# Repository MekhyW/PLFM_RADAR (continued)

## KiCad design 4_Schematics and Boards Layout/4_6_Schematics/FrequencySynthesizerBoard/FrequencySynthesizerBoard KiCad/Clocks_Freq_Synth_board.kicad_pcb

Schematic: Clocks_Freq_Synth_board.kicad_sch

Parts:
C1, C62, C63, C85, C86, C89: 10pF; C0201
C2, C6: 0.33µF; C0201
C3: 0.47µf; C0201
C4, C5, C7: C-EUC0201; C0201
C8: 1000pF; C0201
C9, C10: 0.47µF; C0201
C11, C12, C13, C14, C59, C68, C69, C70, C71, C82: 1µF; C0201
C15, C17, C19: 10nF; C0402
C16, C18, C20, C22, C24, C26, C28, C30, C32, C34, C35, C36, C37, C41, C42, C43, C44, C64, C65, C66, C67, C87, C88, C90, C91: 0.1µF; C0201
C21, C25, C29, C33, C46, C51: 22µF; C1210
C23, C27, C31, C45, C47: 10µF; C1210
C38, C39, C40, C48, C49, C50, C55, C56, C57, C58, C72, C73, C74, C75, C76, C77, C78, C79, C80, C81: 4.7µF; C0201
C60, C83: 31pF; C0201
C61, C84: 10nF; C0201
C92: 0.1µf; C0201
D1, D2: Green; LED-0603
FB1, FB2, FB3, FB4: FBMH1608HL601-T; BEADC1608X90N
IC1: AD9523BCPZ; QFN50P1000X1000X100-73N
J1, J2, J5, J6, J7, J8, J9, J10, J11, J12, J13: 142-0731-211; 1420731211
J3, J4: CJT-T-P-HH-ST-TH1; CONN_CJT-T-P-XX-ST-TH1_SAI
JP1: PINHD-2X6; 2X06
JP2: PINHD-2X7; 2X07
L1, L2, L3, L4, L5, L6, L7, L8: 1.3nH; L0201
L9, L10, L11, L12, L13: L-EUL5650M; L5650M
R1, R12, R13, R26: 100R; R0201
R2, R3, R4, R7, R9, R11: 1k; R0201
R5, R14, R15, R19, R20, R27, R28, R32, R33: 0R; R0201
R6, R8, R10: 0.65k; R0201
R16, R29: 931R; R0201
R17, R30: 30R; R0201
R18, R31: 330R; R0201
R21, R34: 500R; R0201
R22, R23, R24, R25, R35, R36, R37, R38: 200k; R0201
R39, R40, R41: 22R; R0201
U1, U6: ADF4382ABCCZ; CC-48-10_ADI
U2, U3, U7, U9: MTX2-143+; DQ1225_MNC
U4, U5, U8, U10: ATS1005-3DB-FD-T05; SMT_DB-FD-T05_SUS
X4: ECOC-2522-100.000-3HC; SMD5_ECOC-2522_25P4X22_ECS
X5, X6: CVHD-950-50.000; SMD4_CVHD-950_CRX
X10, X11, X12, X13, X14, X15: 22-23-2021

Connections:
10MHZ_OUT: IC1.3 (REFA), X4.4 (OUTPUT)
100MHZ_OUT: IC1.5 (REFB), X5.3 (OUT)
+1V8_CLOCK: C31.1, C35.1, C36.1, C37.1, C41.1, C42.1, C43.1, C44.1, IC1.30 (VDD1.8_OUT[12:13]), IC1.36 (VDD1.8_OUT[10:11]), IC1.42 (VDD1.8_OUT[8:9]), IC1.48 (VDD1.8_OUT[6:7]), IC1.54 (VDD1.8_OUT[4:5]), IC1.63 (VDD1.8_OUT[0:3]), IC1.69 (VDD1.8_PLL2), L11.1
+3V3_CLOCK: C16.1, C18.1, C20.1, C22.1, C24.1, C26.1, C27.1, C28.1, C30.1, C32.1, C34.1, IC1.2 (VDD3_PLL1), IC1.13 (VDD3_PLL2), IC1.18 (VDD3_REF), IC1.27 (VDD3_OUT[12:13]), IC1.33 (VDD3_OUT[10:11]), IC1.39 (VDD3_OUT[8:9]), IC1.45 (VDD3_OUT[6:7]), IC1.51 (VDD3_OUT[4:5]), IC1.60 (VDD3_OUT[2:3]), IC1.66 (VDD3_OUT[0:1]), L10.1
+3V3_LO_1: C38.1, C39.1, C40.1, C45.1, C48.1, C49.1, C50.1, C72.1, C77.1, C78.1, C79.1, C80.1, C81.1, L12.1, R24.2, R25.2, R37.2, R38.2, U1.3 (V3_NDIV), U1.30 (V3_LS), U1.36 (V3_LDO), U1.40 (V3_SYNC), U1.44 (V3_REF), U1.45 (V3_PFD), U6.3 (V3_NDIV), U6.30 (V3_LS), U6.36 (V3_LDO), U6.40 (V3_SYNC), U6.44 (V3_REF), U6.45 (V3_PFD)
+3V3_XO: C23.1, L9.1, R2.2, X4.3 (SUPPLY_VOLTAGE), X5.4 (VDD), X6.4 (VDD)
+5V0_LO: C51.1, FB1.1, FB2.1, FB3.2, FB4.2, X15.1
AD9523_CS: JP1.5, R10.1
AD9523_EEPROM_SEL: IC1.57 (EEPROM_SEL), JP1.11
AD9523_OUT0_N: C11.2, IC1.67 (~OUT0)
AD9523_OUT0_P: C12.2, IC1.68 (OUT0)
AD9523_OUT1_N: C68.2, IC1.64 (~OUT1)
AD9523_OUT1_P: C69.2, IC1.65 (OUT1)
AD9523_OUT2+: IC1.62 (OUT2)
AD9523_OUT2-: IC1.61 (~OUT2)
AD9523_OUT3+: IC1.59 (OUT3)
AD9523_OUT3-: IC1.58 (~OUT3)
AD9523_OUT4_N: IC1.52 (~OUT4), J3.2
AD9523_OUT4_P: IC1.53 (OUT4), J3.1
AD9523_OUT5_N: IC1.49 (~OUT5), J4.2
AD9523_OUT5_P: IC1.50 (OUT5), J4.1
AD9523_OUT6+: C15.2, J7.1
AD9523_OUT7+: IC1.44 (OUT7), J8.1
AD9523_OUT8_N: C70.2, IC1.40 (~OUT8)
AD9523_OUT8_P: C71.2, IC1.41 (OUT8)
AD9523_OUT9_N: C13.2, IC1.37 (~OUT9)
AD9523_OUT9_P: C14.2, IC1.38 (OUT9)
AD9523_OUT10+: IC1.35 (OUT10), R40.1
AD9523_OUT11+: IC1.32 (OUT11), R41.1
AD9523_PD: IC1.15 (~PD), JP1.1
AD9523_REF_SEL: IC1.16 (REF_SEL), JP1.2
AD9523_RESET: IC1.19 (~RESET), JP1.4
AD9523_SCLK: JP1.6, R6.1
AD9523_SDIO: JP1.7, R8.1
AD9523_SDO: IC1.23 (SDO), JP1.8
AD9523_STATUS0: IC1.56 (STATUS0/SP0), JP1.9
AD9523_STATUS1: IC1.55 (STATUS1/SPI), JP1.10
AD9523_SYNC: IC1.17 (~SYNC), JP1.3
ADF4382_RX_CE: JP2.10, R38.1, U6.31 (CE)
ADF4382_RX_CS: JP2.9, R37.1, U6.32 (CSB)
ADF4382_RX_DELADJ: JP2.12, R35.2, U6.28 (DELADJ)
ADF4382_RX_DELSTR: JP2.11, R36.2, U6.29 (DELSTR)
ADF4382_RX_LKDET: JP2.13, R34.2, U6.27 (LKDET)
ADF4382_RX_SYNC_N: C70.1, R26.2, U6.39 (SYNCN)
ADF4382_RX_SYNC_P: C71.1, R26.1, U6.38 (SYNCP)
ADF4382_SCLK: JP2.2, U1.34 (SCLK), U6.34 (SCLK)
ADF4382_SDIO: JP2.3, U1.33 (SDIO), U6.33 (SDIO)
ADF4382_SDO: JP2.1, U1.35 (SDO), U6.35 (SDO)
ADF4382_TX_CE: JP2.5, R25.1, U1.31 (CE)
ADF4382_TX_CS: JP2.4, R24.1, U1.32 (CSB)
ADF4382_TX_DELADJ: JP2.7, R22.2, U1.28 (DELADJ)
ADF4382_TX_DELSTR: JP2.6, R23.2, U1.29 (DELSTR)
ADF4382_TX_LKDET: JP2.8, R21.2, U1.27 (LKDET)
ADF4382_TX_SYNC_N: C13.1, R13.2, U1.39 (SYNCN)
ADF4382_TX_SYNC_P: C14.1, R13.1, U1.38 (SYNCP)
GND: C1.2, C2.2, C3.1, C4.1, C5.1, C6.1, C7.1, C9.1, C10.1, C16.2, C18.2, C20.2, C21.2, C22.2, C23.2, C24.2, C25.2, C26.2, C27.2, C28.2, C29.2, C30.2, C31.2, C32.2, C33.2, C34.2, C35.2, C36.2, C37.2, C38.2, C39.2, C40.2, C41.2, C42.2, C43.2, C44.2, C45.2, C46.2, C47.2, C48.2, C49.2, C50.2, C51.2, C55.2, C56.2, C57.2, C58.2, C59.1, C60.2, C61.2, C62.2, C63.2, C72.2, C73.2, C74.2, C75.2, C76.2, C77.2, C78.2, C79.2, C80.2, C81.2, C82.1, C83.2, C84.2, C85.2, C86.2, C89.2, D1.C, D2.C, IC1.73 (EP), J1.2, J1.3, J1.4, J1.5, J2.2, J2.3, J2.4, J2.5, J5.2, J5.3, J5.4, J5.5, J6.2, J6.3, J6.4, J6.5, J7.2, J7.3, J7.4, J7.5, J8.2, J8.3, J8.4, J8.5, J9.2, J9.3, J9.4, J9.5, J10.2, J10.3, J10.4, J10.5, J11.2, J11.3, J11.4, J11.5, J12.2, J12.3, J12.4, J12.5, J13.2, J13.3, J13.4, J13.5, JP1.12, JP2.14, R3.1, R7.2, R9.2, R11.2, R22.1, R23.1, R35.1, R36.1, U1.1 (GND_2), U1.2 (GND_3), U1.4 (GND_4), U1.10 (GND_5), U1.12 (GND_6), U1.14 (GND_7), U1.16 (GND_8), U1.18 (GND_9), U1.19 (GND_10), U1.21 (GND_11), U1.23 (GND_12), U1.25 (GND_13), U1.26 (GND_14), U1.41 (GND_15), U1.48 (GND_16), U1.49 (GND_17), U1.50 (GND_18), U1.51 (GND_19), U1.52 (GND), U2.1 (EXTERNAL_GND_2), U2.3 (EXTERNAL_GND_3), U2.6 (EXTERNAL_GND_4), U2.10 (EXTERNAL_GND_5), U2.13 (EXTERNAL_GND), U3.1 (EXTERNAL_GND_2), U3.3 (EXTERNAL_GND_3), U3.6 (EXTERNAL_GND_4), U3.10 (EXTERNAL_GND_5), U3.13 (EXTERNAL_GND), U4.3 (GND_2), U4.4 (GND), U5.3 (GND_2), U5.4 (GND), U6.1 (GND_2), U6.2 (GND_3), U6.4 (GND_4), U6.10 (GND_5), U6.12 (GND_6), U6.14 (GND_7), U6.16 (GND_8), U6.18 (GND_9), U6.19 (GND_10), U6.21 (GND_11), U6.23 (GND_12), U6.25 (GND_13), U6.26 (GND_14), U6.41 (GND_15), U6.48 (GND_16), U6.49 (GND_17), U6.50 (GND_18), U6.51 (GND_19), U6.52 (GND), U7.1 (EXTERNAL_GND_2), U7.3 (EXTERNAL_GND_3), U7.6 (EXTERNAL_GND_4), U7.10 (EXTERNAL_GND_5), U7.13 (EXTERNAL_GND), U8.3 (GND_2), U8.4 (GND), U9.1 (EXTERNAL_GND_2), U9.3 (EXTERNAL_GND_3), U9.6 (EXTERNAL_GND_4), U9.10 (EXTERNAL_GND_5), U9.13 (EXTERNAL_GND), U10.3 (GND_2), U10.4 (GND), X4.5 (GROUND), X5.2 (GND), X6.2 (GND), X10.2, X11.2, X12.2, X13.2, X14.2, X15.2
unnamed: R2.1, R3.2, X4.1 (VOLTAGE_CONTROL)
unnamed: C2.1, R4.1, X6.1 (VOLT_CONTROL)
unnamed: C3.2, IC1.1 (LDO_PLL1)
unnamed: C6.2, IC1.7 (LF1_EXT_CAP)
unnamed: C4.2, IC1.4 (~REFA)
unnamed: C5.2, IC1.6 (~REFB)
unnamed: C7.2, IC1.10 (~OSC_IN)
unnamed: C8.2, IC1.11 (LF2_EXT_CAP)
unnamed: C8.1, R5.1
unnamed: C9.2, IC1.14 (LDO_VCO), R5.2
unnamed: C10.2, IC1.12 (LDO_PLL2)
unnamed: IC1.21 (SCLK/SCL), R6.2, R7.1
unnamed: IC1.22 (SDIO/SDA), R8.2, R9.1
unnamed: IC1.20 (~CS), R10.2, R11.1
unnamed: C11.1, R12.2, U1.43 (REFN)
unnamed: C12.1, R12.1, U1.42 (REFP)
unnamed: C61.1, R18.2
unnamed: R14.1, U1.9 (V5_VCO)
unnamed: FB2.2, R14.2, U1.8 (V5_CAL)
unnamed: C59.2, FB3.1, U1.46 (V5_CP)
unnamed: R19.1, R20.2
unnamed: R15.1, U1.7 (VTUNE)
unnamed: R15.2, R16.2
unnamed: C60.1, R16.1, R17.2
unnamed: R17.1, R18.1, R19.2
unnamed: C62.1, R20.1, U1.47 (CP)
unnamed: U2.2 (PRIMARY_DOT), U4.1 (INPUT)
unnamed: C65.2, U2.7 (SECONDARY_DOT)
unnamed: J10.1, U4.2 (OUTPUT)
unnamed: C64.2, U2.9 (SECONDARY)
unnamed: C67.2, U3.7 (SECONDARY_DOT)
unnamed: C66.2, U3.9 (SECONDARY)
unnamed: U3.2 (PRIMARY_DOT), U5.1 (INPUT)
unnamed: J1.1, U5.2 (OUTPUT)
unnamed: D1.A, R21.1
unnamed: J9.1, U1.37 (MUXOUT)
unnamed: C68.1, R1.2, U6.43 (REFN)
unnamed: C69.1, R1.1, U6.42 (REFP)
unnamed: R27.1, U6.9 (V5_VCO)
unnamed: FB1.2, R27.2, U6.8 (V5_CAL)
unnamed: C82.2, FB4.1, U6.46 (V5_CP)
unnamed: C84.1, R31.2
unnamed: R32.1, R33.2
unnamed: R28.1, U6.7 (VTUNE)
unnamed: R28.2, R29.2
unnamed: C83.1, R29.1, R30.2
unnamed: R30.1, R31.1, R32.2
unnamed: C85.1, R33.1, U6.47 (CP)
unnamed: D2.A, R34.1
unnamed: J2.1, U6.37 (MUXOUT)
unnamed: C88.2, U7.7 (SECONDARY_DOT)
unnamed: C87.2, U7.9 (SECONDARY)
unnamed: U7.2 (PRIMARY_DOT), U8.1 (INPUT)
unnamed: J11.1, U8.2 (OUTPUT)
unnamed: C91.2, U9.7 (SECONDARY_DOT)
unnamed: C90.2, U9.9 (SECONDARY)
unnamed: U9.2 (PRIMARY_DOT), U10.1 (INPUT)
unnamed: J12.1, U10.2 (OUTPUT)
unnamed: C92.1, IC1.72 (~PLL_OUT)
unnamed: C92.2, J13.1
unnamed: IC1.47 (OUT6), R39.1
unnamed: C15.1, R39.2
unnamed: C17.2, J5.1
unnamed: C17.1, R40.2
unnamed: C19.2, J6.1
unnamed: C19.1, R41.2
unnamed: C21.1, L9.2, X10.1
unnamed: C25.1, L10.2, X11.1
unnamed: C29.1, L11.2, X12.1
unnamed: C33.1, L12.2, X13.1
unnamed: C46.1, L13.2, X14.1
OSC_CTRL: IC1.8 (OSC_CTRL), R4.2
RX_RFOUT_1_N: C87.1, L5.2, U6.20 (RFOUT1N)
RX_RFOUT_1_P: C88.1, L6.1, U6.22 (RFOUT1P)
RX_RFOUT_2_N: C90.1, L7.2, U6.15 (RFOUT2N)
RX_RFOUT_2_P: C91.1, L8.1, U6.17 (RFOUT2P)
TX_RFOUT_1_N: C64.1, L2.2, U1.20 (RFOUT1N)
TX_RFOUT_1_P: C65.1, L3.1, U1.22 (RFOUT1P)
TX_RFOUT_2_N: C66.1, L1.2, U1.15 (RFOUT2N)
TX_RFOUT_2_P: C67.1, L4.1, U1.17 (RFOUT2P)
VCXO_OUT: IC1.9 (OSC_IN), X6.3 (OUT)

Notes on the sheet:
L9 to L13: MPN HI2220P601R-10 FERRITE BEAD 600 OHM 2220 (5650) 1LN
C:/Users/ASUS/Desktop/RADAR_V5/EagleFiles/FrequencySynthesizerBoard/clock_planning.bmp
60 MHz
Jitter Cleaner, Clock Generator & Frequency Synthesizer
CCHD-950-100.000
CVHD-950-100.000

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
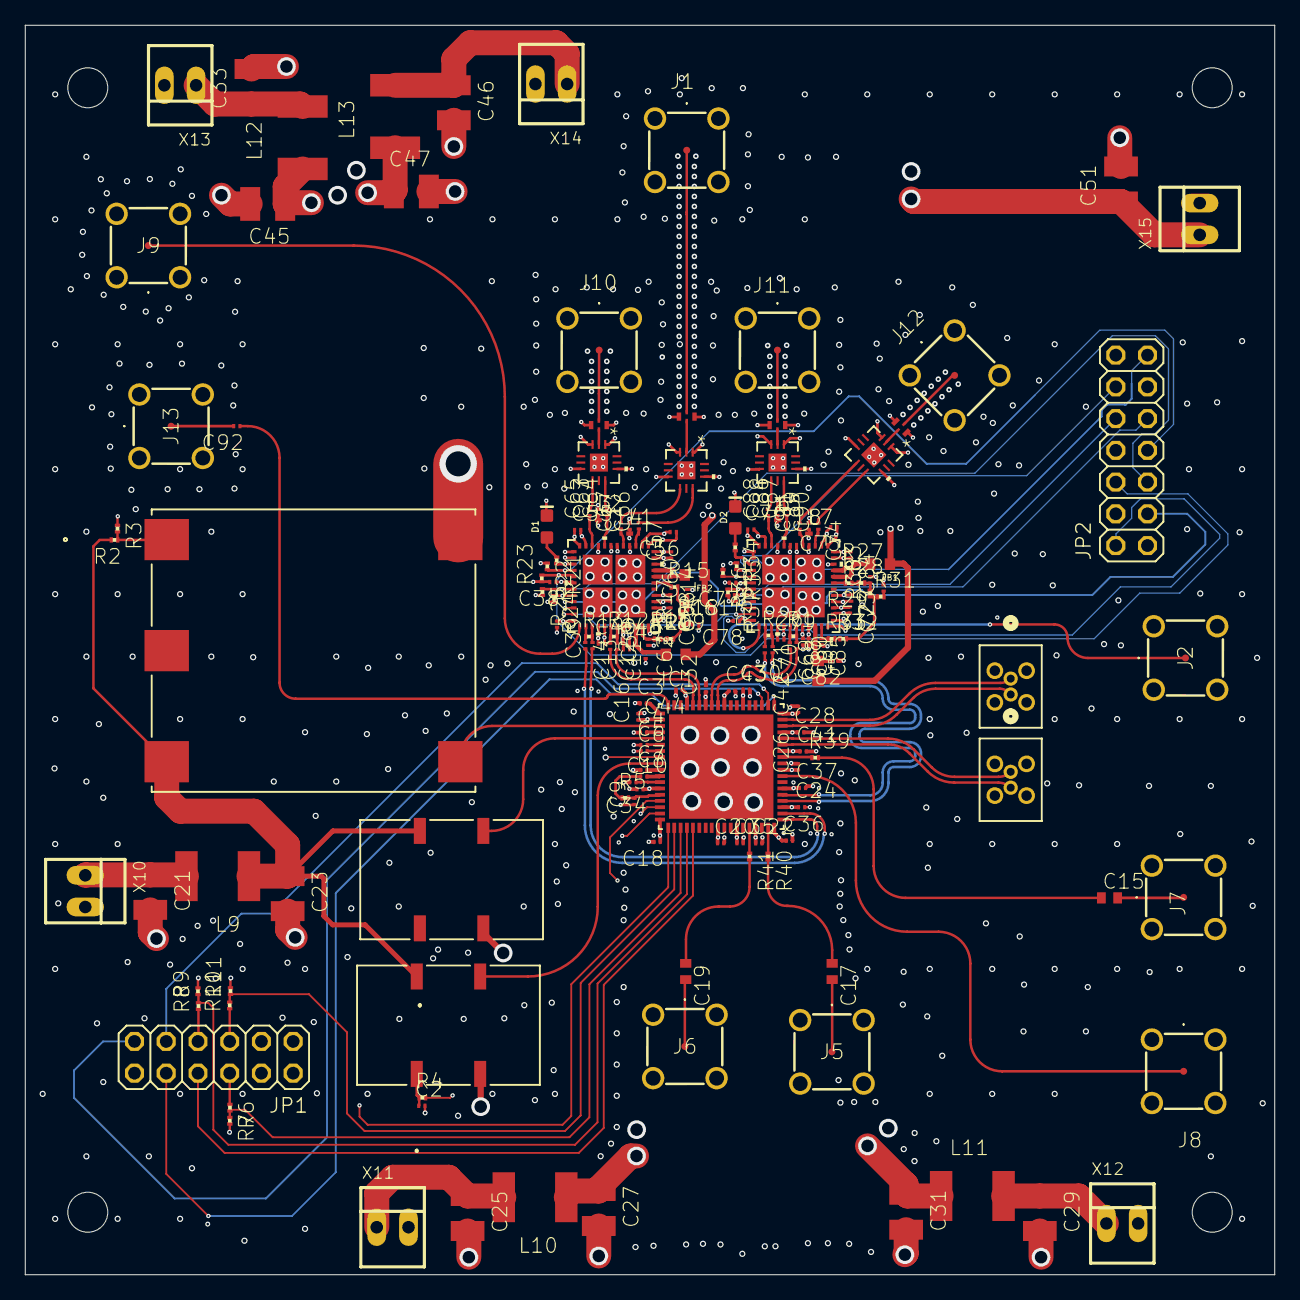
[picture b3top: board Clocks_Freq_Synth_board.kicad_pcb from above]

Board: 6 copper layers, 100.0 x 100.0 mm, 188 parts (0 on the bottom side), 134 nets.

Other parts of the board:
UNK_HOLE_0: dummyfp0
UNK_HOLE_1: dummyfp1
UNK_HOLE_2: dummyfp2
UNK_HOLE_3: dummyfp3

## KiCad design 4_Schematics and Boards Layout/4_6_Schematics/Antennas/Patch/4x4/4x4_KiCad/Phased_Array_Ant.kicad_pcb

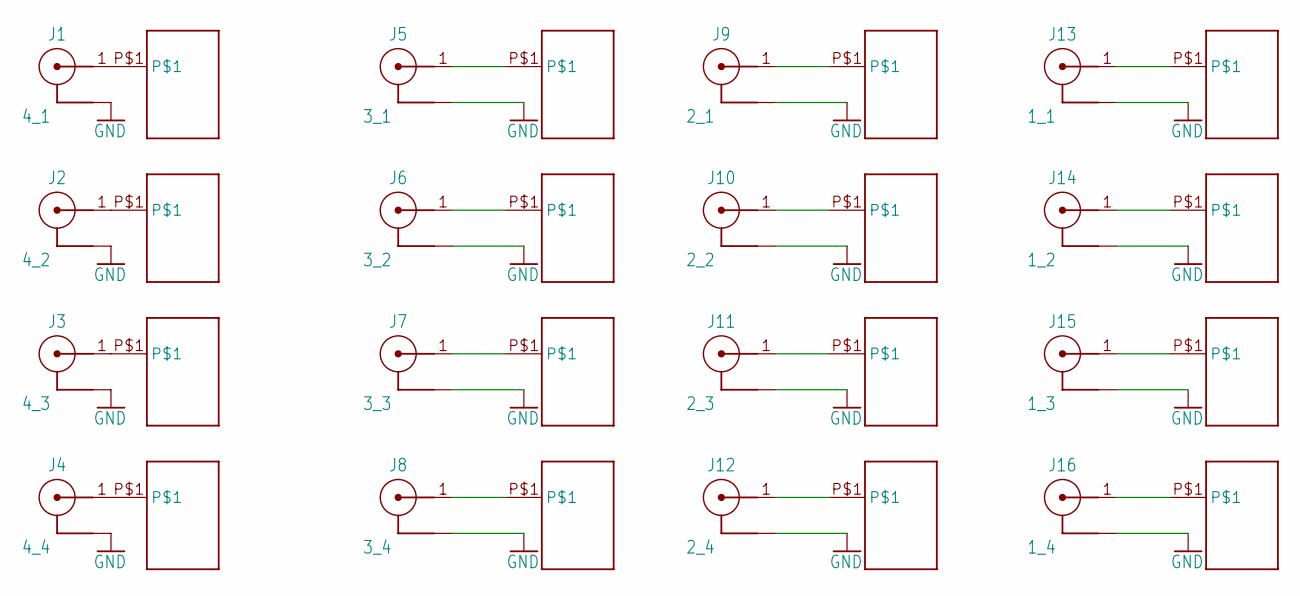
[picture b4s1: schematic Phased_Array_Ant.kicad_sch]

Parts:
J1: 4_1; 60124102122403
J2: 4_2; 60124102122403
J3: 4_3; 60124102122403
J4: 4_4; 60124102122403
J5: 3_1; 60124102122403
J6: 3_2; 60124102122403
J7: 3_3; 60124102122403
J8: 3_4; 60124102122403
J9: 2_1; 60124102122403
J10: 2_2; 60124102122403
J11: 2_3; 60124102122403
J12: 2_4; 60124102122403
J13: 1_1; 60124102122403
J14: 1_2; 60124102122403
J15: 1_3; 60124102122403
J16: 1_4; 60124102122403
U$1, U$2, U$3, U$4, U$5, U$6, U$7, U$8, U$9, U$10, U$11, U$12, U$13, U$14, U$15, U$16: 10.5GHZ_ANT

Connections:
GND: J1.2, J1.3 (2), J1.4 (2), J2.2, J2.3 (2), J2.4 (2), J3.2, J3.3 (2), J3.4 (2), J4.2, J4.3 (2), J4.4 (2), J5.2, J5.3 (2), J5.4 (2), J6.2, J6.3 (2), J6.4 (2), J7.2, J7.3 (2), J7.4 (2), J8.2, J8.3 (2), J8.4 (2), J9.2, J9.3 (2), J9.4 (2), J10.2, J10.3 (2), J10.4 (2), J11.2, J11.3 (2), J11.4 (2), J12.2, J12.3 (2), J12.4 (2), J13.2, J13.3 (2), J13.4 (2), J14.2, J14.3 (2), J14.4 (2), J15.2, J15.3 (2), J15.4 (2), J16.2, J16.3 (2), J16.4 (2)
unnamed: J1.1, U$1.P$1
unnamed: J2.1, U$2.P$1
unnamed: J3.1, U$3.P$1
unnamed: J4.1, U$4.P$1
unnamed: J5.1, U$5.P$1
unnamed: J6.1, U$6.P$1
unnamed: J7.1, U$7.P$1
unnamed: J8.1, U$8.P$1
unnamed: J9.1, U$9.P$1
unnamed: J10.1, U$10.P$1
unnamed: J11.1, U$11.P$1
unnamed: J12.1, U$12.P$1
unnamed: J13.1, U$13.P$1
unnamed: J14.1, U$14.P$1
unnamed: J15.1, U$15.P$1
unnamed: J16.1, U$16.P$1

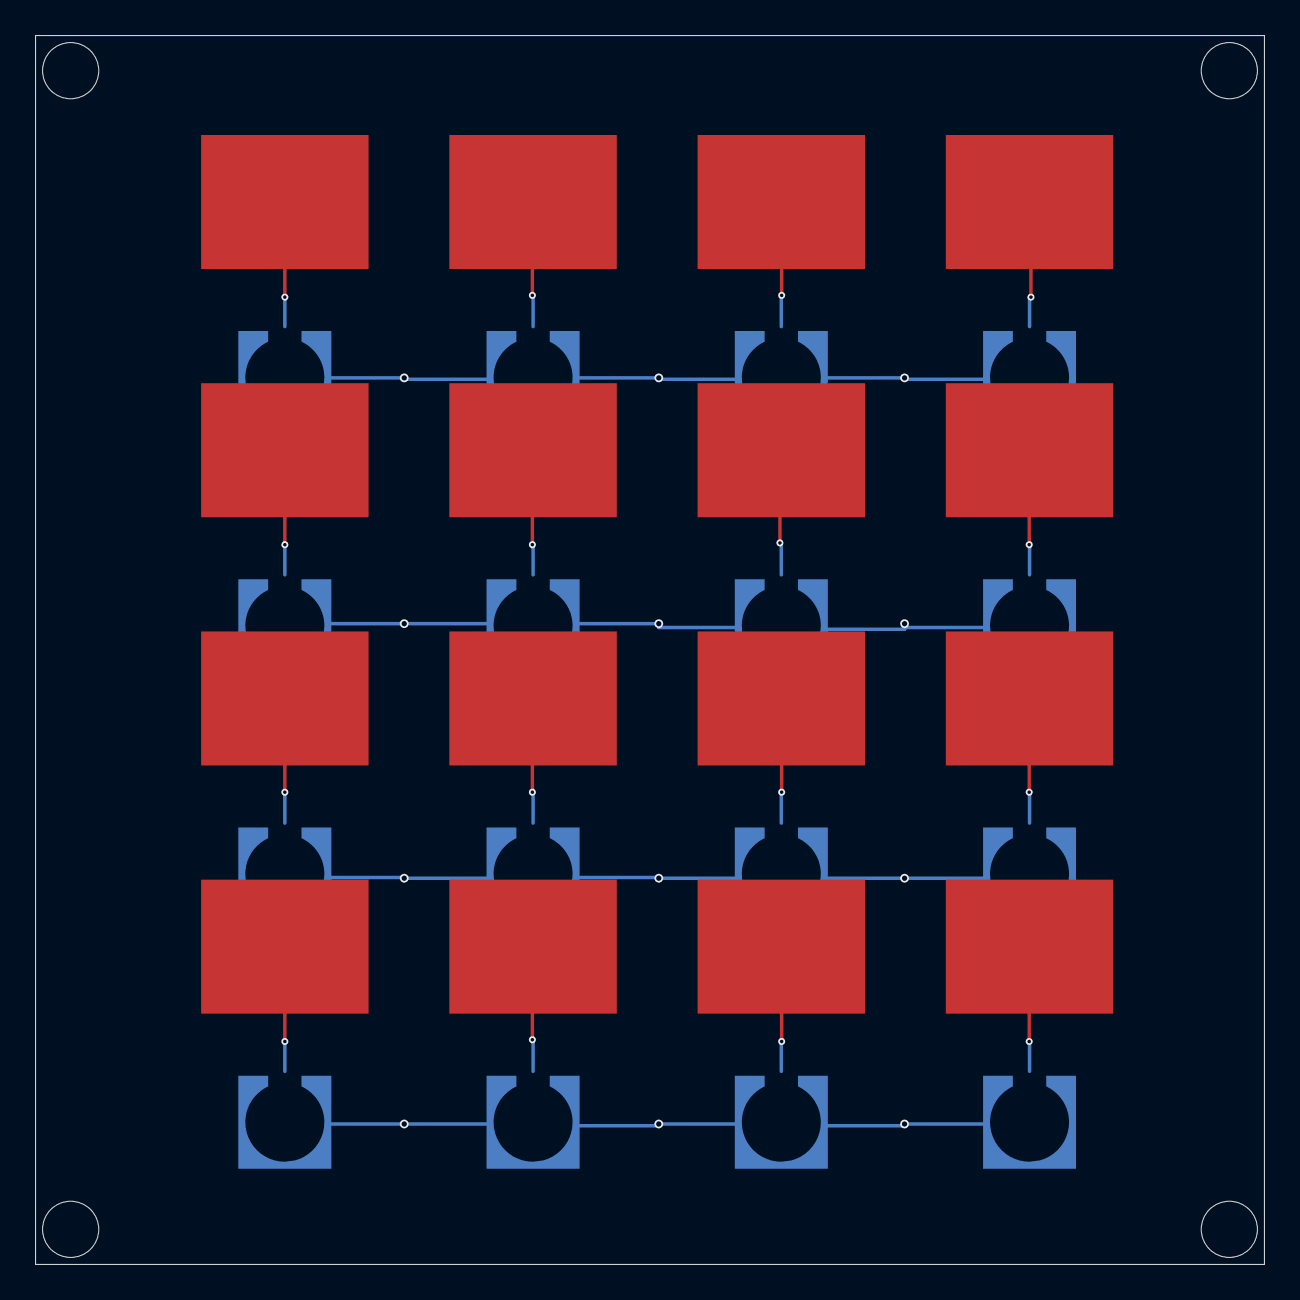
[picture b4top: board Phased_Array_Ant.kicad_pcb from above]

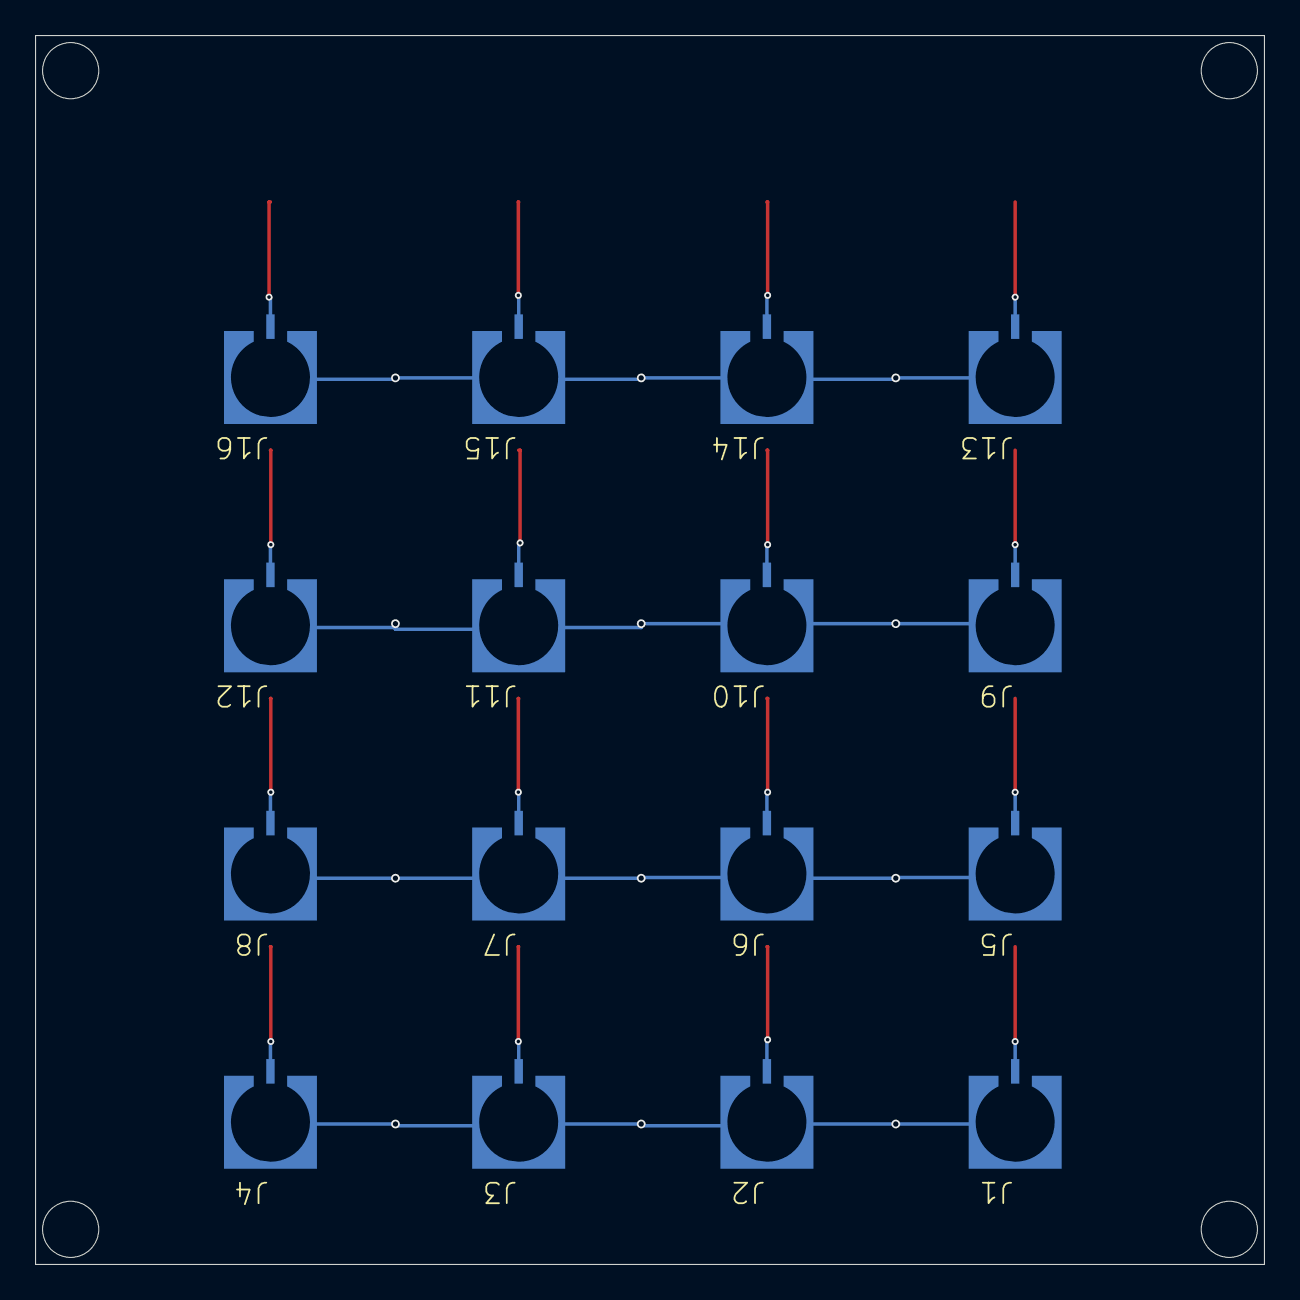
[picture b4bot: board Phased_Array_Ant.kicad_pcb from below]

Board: 6 copper layers, 70.0 x 70.0 mm, 36 parts (16 on the bottom side), 17 nets.

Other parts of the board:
UNK_HOLE_0: dummyfp0
UNK_HOLE_1: dummyfp1
UNK_HOLE_2: dummyfp2
UNK_HOLE_3: dummyfp3

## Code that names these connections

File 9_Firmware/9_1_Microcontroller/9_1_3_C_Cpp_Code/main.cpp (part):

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};

// Convenience HAL wrappers for AD9523 control pins (GPIOF as you said)
static inline void AD9523_PD(bool v)        { HAL_GPIO_WritePin(GPIOF, AD9523_PD_Pin, v ? GPIO_PIN_SET : GPIO_PIN_RESET); }
static inline void AD9523_REF_SEL(bool v)   { HAL_GPIO_WritePin(GPIOF, AD9523_REF_SEL_Pin, v ? GPIO_PIN_SET : GPIO_PIN_RESET); }
static inline void AD9523_SYNC_PULSE(void)  { HAL_GPIO_WritePin(GPIOF, AD9523_SYNC_Pin, GPIO_PIN_SET); HAL_Delay(1); HAL_GPIO_WritePin(GPIOF, AD9523_SYNC_Pin, GPIO_PIN_RESET); }
static inline void AD9523_RESET_ASSERT()    { HAL_GPIO_WritePin(GPIOF, AD9523_RESET_Pin, GPIO_PIN_RESET); } // check polarity
static inline void AD9523_RESET_RELEASE()   { HAL_GPIO_WritePin(GPIOF, AD9523_RESET_Pin, GPIO_PIN_SET); }
static inline void AD9523_CS(bool v)        { HAL_GPIO_WritePin(GPIOF, AD9523_CS_Pin, v ? GPIO_PIN_SET : GPIO_PIN_RESET); }
static inline void AD9523_EEPROM_SEL(bool v){ HAL_GPIO_WritePin(GPIOF, AD9523_EEPROM_SEL_Pin, v ? GPIO_PIN_SET : GPIO_PIN_RESET); }

/* USER CODE END PV */

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    static uint32_t last_clock_check = 0;
    if (HAL_GetTick() - last_clock_check > 5000) {
        last_clock_check = HAL_GetTick();   // commit the rate-limit window first
        GPIO_PinState s0 = HAL_GPIO_ReadPin(AD9523_STATUS0_GPIO_Port, AD9523_STATUS0_Pin);
        GPIO_PinState s1 = HAL_GPIO_ReadPin(AD9523_STATUS1_GPIO_Port, AD9523_STATUS1_Pin);
        DIAG_GPIO("CLK", "AD9523 STATUS0", s0);
        DIAG_GPIO("CLK", "AD9523 STATUS1", s1);
        if (s0 == GPIO_PIN_RESET || s1 == GPIO_PIN_RESET) {
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
  DIAG_SECTION("AD9523 POWER SEQUENCING");
  DIAG("PWR", "Asserting AD9523 reset (pin LOW)");
  HAL_GPIO_WritePin(AD9523_RESET_GPIO_Port,AD9523_RESET_Pin,GPIO_PIN_RESET);

  //Power sequencing AD9523
  DIAG("PWR", "Enabling 1.8V clock rail");
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
  // check if there is a lock via direct GPIO (independent of register read above)
  DIAG("LO", "Direct GPIO lock detect pins:");
  DIAG_GPIO("LO", "ADF4382_TX_LKDET", ADF4382_TX_LKDET_GPIO_Port, ADF4382_TX_LKDET_Pin);
  DIAG_GPIO("LO", "ADF4382_RX_LKDET", ADF4382_RX_LKDET_GPIO_Port, ADF4382_RX_LKDET_Pin);
  if(HAL_GPIO_ReadPin (ADF4382_TX_LKDET_GPIO_Port, ADF4382_TX_LKDET_Pin))
  {
      // Set The LED_1 ON!
      HAL_GPIO_WritePin(LED_1_GPIO_Port, LED_1_Pin, GPIO_PIN_SET);
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      DIAG_WARN("LO", "TX NOT locked via GPIO -- LED_1 OFF");
  }

  if(HAL_GPIO_ReadPin (ADF4382_RX_LKDET_GPIO_Port, ADF4382_RX_LKDET_Pin))
  {
      // Set The LED_2 ON!
      HAL_GPIO_WritePin(LED_2_GPIO_Port, LED_2_Pin, GPIO_PIN_SET);
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  __HAL_RCC_GPIOD_CLK_ENABLE();

  /*Configure GPIO pin Output Level */
  HAL_GPIO_WritePin(GPIOF, AD9523_PD_Pin|AD9523_REF_SEL_Pin|AD9523_SYNC_Pin|AD9523_RESET_Pin
                          |AD9523_CS_Pin|AD9523_EEPROM_SEL_Pin|LED_1_Pin|LED_2_Pin
                          |LED_3_Pin|LED_4_Pin, GPIO_PIN_RESET);

  /*Configure GPIO pin Output Level */
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
  /*Configure GPIO pin Output Level */
  HAL_GPIO_WritePin(GPIOG, EN_P_5V0_PA1_Pin|EN_P_5V0_PA2_Pin|EN_P_5V0_PA3_Pin|EN_P_5V5_PA_Pin
                          |EN_P_1V8_CLOCK_Pin|EN_P_3V3_CLOCK_Pin|ADF4382_RX_DELADJ_Pin|ADF4382_RX_DELSTR_Pin
                          |ADF4382_RX_CE_Pin|ADF4382_RX_CS_Pin|ADF4382_TX_DELSTR_Pin|ADF4382_TX_DELADJ_Pin
                          |ADF4382_TX_CS_Pin|ADF4382_TX_CE_Pin, GPIO_PIN_RESET);

  /*Configure GPIO pin Output Level */
  HAL_GPIO_WritePin(GPIOE, EN_P_1V0_FPGA_Pin|EN_P_1V8_FPGA_Pin|EN_P_3V3_FPGA_Pin|EN_P_5V0_ADAR_Pin
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  /*Configure GPIO pin Output Level */
  HAL_GPIO_WritePin(GPIOB, DAC_1_VG_CLR_Pin|DAC_1_VG_LDAC_Pin|DAC_2_VG_CLR_Pin|DAC_2_VG_LDAC_Pin, GPIO_PIN_RESET);

  /*Configure GPIO pins : AD9523_PD_Pin AD9523_REF_SEL_Pin AD9523_SYNC_Pin AD9523_RESET_Pin
                           AD9523_CS_Pin AD9523_EEPROM_SEL_Pin LED_1_Pin LED_2_Pin
                           LED_3_Pin LED_4_Pin */
  GPIO_InitStruct.Pin = AD9523_PD_Pin|AD9523_REF_SEL_Pin|AD9523_SYNC_Pin|AD9523_RESET_Pin
                          |AD9523_CS_Pin|AD9523_EEPROM_SEL_Pin|LED_1_Pin|LED_2_Pin
                          |LED_3_Pin|LED_4_Pin;
  GPIO_InitStruct.Mode = GPIO_MODE_OUTPUT_PP;
  GPIO_InitStruct.Pull = GPIO_NOPULL;
  GPIO_InitStruct.Speed = GPIO_SPEED_FREQ_LOW;
  HAL_GPIO_Init(GPIOF, &GPIO_InitStruct);

  /*Configure GPIO pins : AD9523_STATUS0_Pin AD9523_STATUS1_Pin */
  GPIO_InitStruct.Pin = AD9523_STATUS0_Pin|AD9523_STATUS1_Pin;
  GPIO_InitStruct.Mode = GPIO_MODE_INPUT;
  GPIO_InitStruct.Pull = GPIO_NOPULL;
  HAL_GPIO_Init(GPIOF, &GPIO_InitStruct);
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  HAL_GPIO_Init(GPIOA, &GPIO_InitStruct);

  /*Configure GPIO pins : EN_P_5V0_PA1_Pin EN_P_5V0_PA2_Pin EN_P_5V0_PA3_Pin EN_P_5V5_PA_Pin
                           EN_P_1V8_CLOCK_Pin EN_P_3V3_CLOCK_Pin ADF4382_RX_DELADJ_Pin ADF4382_RX_DELSTR_Pin
                           ADF4382_RX_CE_Pin ADF4382_RX_CS_Pin ADF4382_TX_DELSTR_Pin ADF4382_TX_DELADJ_Pin
                           ADF4382_TX_CS_Pin ADF4382_TX_CE_Pin */
  GPIO_InitStruct.Pin = EN_P_5V0_PA1_Pin|EN_P_5V0_PA2_Pin|EN_P_5V0_PA3_Pin|EN_P_5V5_PA_Pin
                          |EN_P_1V8_CLOCK_Pin|EN_P_3V3_CLOCK_Pin|ADF4382_RX_DELADJ_Pin|ADF4382_RX_DELSTR_Pin
                          |ADF4382_RX_CE_Pin|ADF4382_RX_CS_Pin|ADF4382_TX_DELSTR_Pin|ADF4382_TX_DELADJ_Pin
                          |ADF4382_TX_CS_Pin|ADF4382_TX_CE_Pin;
  GPIO_InitStruct.Mode = GPIO_MODE_OUTPUT_PP;
  GPIO_InitStruct.Pull = GPIO_NOPULL;
  GPIO_InitStruct.Speed = GPIO_SPEED_FREQ_LOW;
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  HAL_NVIC_SetPriority(FPGA_FRAME_PULSE_EXTI_IRQn, 5, 0);
  HAL_NVIC_EnableIRQ(FPGA_FRAME_PULSE_EXTI_IRQn);

  /*Configure GPIO pins : ADF4382_RX_LKDET_Pin ADF4382_TX_LKDET_Pin */
  GPIO_InitStruct.Pin = ADF4382_RX_LKDET_Pin|ADF4382_TX_LKDET_Pin;
  GPIO_InitStruct.Mode = GPIO_MODE_INPUT;
  GPIO_InitStruct.Pull = GPIO_NOPULL;
  HAL_GPIO_Init(GPIOG, &GPIO_InitStruct);
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
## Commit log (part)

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2026-04-18 fix(fpga): registered reset fan-out at 400 MHz; default USB to FT2232H
    Replace direct !reset_n async sense with a registered active-high reset_h
    (max_fanout=50) in nco_400m_enhanced, cic_decimator_4x_enhanced, and
    ddc_400m. The prior single-LUT1 / 700+ load net was the root cause of
    WNS=-0.626 ns in the 400 MHz clock domain on the xc7a50t build. Vivado
    replicates the constrained register into ≈14 regional copies, each driving
    ≤50 loads, closing timing at 2.5 ns.
2026-04-23 ci(fpga): wire RX-B latency tests; fix downstream compile after inline-FFT removal
    - run_regression.sh: add frequency_matched_filter.v to PROD_RTL and RECEIVER_RTL
    compile groups (was implicitly required after inline behavioural FFT in
    matched_filter_processing_chain.v was removed); empty EXTRA_RTL with set -u
    guards; bump Matched Filter Chain timeout to 600s.
    - run_regression.sh: add two PHASE 3 tests — tb_rxb_latency_measure (chain
    pipeline depth) and tb_rxb_fullchain_latency (multi-segment + chain).
2026-04-23 perf(fpga): symmetric pre-adder FIR — 32→16 DSPs/channel (-32 total)
    Re-group the 32-tap symmetric lowpass into 16 (D+A)*B operations using
    the DSP48E1 pre-adder, exploiting coeff[k] == coeff[31-k]. Production
    silicon (XC7A50T) drops from 112/120 DSPs (93.3%) to 80/120 (66.7%),
    freeing the budget needed for the matched-filter FFT swap (RX-NEW-3).
    Bit-exact contract preserved at non-saturating signal levels: DC=5000
    → 8847 and 45 MHz tone → ±16 LSB match the unfolded design and the
2026-04-27 cleanup(fpga): RX-A1 — drop dead chirp_counter port from MF chain
    matched_filter_processing_chain declared `input wire [5:0] chirp_counter`
    but never read it inside the module. matched_filter_multi_segment passed
    its own chirp_counter through to that dead port.
    Removed the port from the chain and the corresponding hookup at the
    multi_segment instantiation site. Five testbenches also referenced the
    port (tb_mf_cosim, tb_matched_filter_processing_chain, tb_rxb_latency
2026-04-28 fix(mcu): MCU-A6 — recovery handlers for AD9523_CLOCK and FPGA_COMM
    attemptErrorRecovery() previously fell through to the default log-only
    branch for both ERROR_AD9523_CLOCK and ERROR_FPGA_COMM. checkSystemHealth
    keeps re-firing the same error every pass with no recovery action ever
    attempted, so the system limps along until escalation kicks in.
    ERROR_AD9523_CLOCK: AD9523_RESET_ASSERT, 10 ms settle, then re-run
    configure_ad9523() (releases reset, selects REFB, reprograms, waits for
2026-04-29 mcu(bmp180): call cal-coefficient init at boot + watchdog cadence fix (AUDIT-CAL)
    The BMP180 driver had no public init method and never called
    readCalibrationCoefficients() from anywhere -- _calCoeff ran at the
    C++ in-class member-initializer defaults (all zeros) at runtime.
    Consequence chain:
    - computeB5(UT) short-circuited via 0/0 (Cortex-M7 SDIV with
    SCB->CCR.DIV_0_TRP=0 returns 0 silently -- system_stm32f7xx.c does
2026-04-29 mcu(health): commit rate-limit window before early returns (AUDIT-CAL follow-up)
    checkSystemHealth() had three watchdog blocks with the identical
    "last_X_check not updated on error path" bug — same root cause as
    AUDIT-CAL (BMP180 fix in commit 95aed35), distinct sites:
    AD9523 clock check (5 s) main.cpp:693-705
    ADAR1000 comm check (2 s) main.cpp:729-749
    IMU comm check (10 s) main.cpp:752-760
2026-04-30 docs(fpga): correct matched_filter_processing_chain header (LogiCORE swap, FSM)
    The header still described the legacy in-house Radix-2 DIT fft_engine and a
    FWD/REF/INV BITREV+BUTTERFLY state list that no longer matches reality.
    Since RX-NEW-3 (commit 5c8cc8c), the chain instantiates fft_engine_axi_bridge,
    which wraps xfft_2048 — LogiCORE FFT v9.1 (Pipelined Streaming) in synth/XSim
    when FFT_USE_XILINX_IP is defined, in-house fft_engine fallback in iverilog.
    Bit-reversal is now handled inside the IP (and the fallback), so the FSM has
2026-04-30 chirp-v2 PR-D: chirp_scheduler replaces radar_mode_controller; MF/MTI wave_sel-native
    Single 100 MHz scheduler emits wave_sel[1:0] and chirp_pulse natively. Modes
    00 (STM32 pass-through), 01 (auto-scan over SHORT/MEDIUM/LONG sub-frames),
    10 (single-chirp debug), 11 (track dwell with watchdog scan-fallback after
    RP_DEF_TRACK_WATCHDOG_FRAMES=5 idle frames). Sub-frame mask lets ops drop a
    waveform without recompiling.
    Drops the receiver_final wave_sel shim added in PR-C: wave_sel comes
2026-05-01 fix(regression): allow leading whitespace in [PASS]/[FAIL] anchors
    Three regex sites (run_test, run_mf_cosim, run_doppler_cosim) anchored
    at column 0 with `^\[PASS|^\[FAIL`, but most TBs emit ` [PASS]` /
    ` [FAIL]` from `task check;` formatting. Anchors silently matched
    zero markers, the fallback "did anything reach $finish" path
    reported PASS, and 48 real failures across tb_system_e2e (×2 modes),
    tb_fft_engine, and tb_fullchain_realdata went unnoticed across PR-D..G.
2026-05-01 test(fft): PR-L — fix tb_fft_engine N=32→16 dropdown bugs (T-4)
    The TB hard-coded /32.0 in cosine/sine angle math and read out_re[28] /
    out_re[30] which don't exist for N=16, so 3/12 checks failed (Test 3
    single-tone, Test 7 imag-tone). Pure TB math error — fft_engine.v is
    correct (proven by every production MF/Doppler cosim passing bit-exact).
    Test 3: /32.0 → /N, peak expected = N/2*1000 = 8000 (not 16000),
    conjugate read at bin N-4=12 (not 28).
2026-05-01 fix(fpga): C-4 — replace IDDR DDR demux with negedge IFF for AD9484 SDR
    The AD9484 is SDR LVDS — datasheet p.5 lists "Output (LVDS—SDR)" as the
    only output mode and p.16 confirms "data outputs are valid on the rising
    edge of DCO." DCO runs at fs (400 MHz), one new sample per period, held
    stable across the period. There is no DDR mode and no SPI access (CSB is
    tied to +1V8 on the production board, RADAR_Main_Board.sch:46719).
    ad9484_interface_400m.v previously instantiated an IDDR per data bit and
2026-05-02 fix(fpga): PR-O.8.1 — drop stale BFP-era ports, fix xsim include path
    Wrapper xfft_2048.v had m_axis_data_tuser and m_axis_status_{tdata,tvalid,
    tready} hooked up to the IP, but the regenerated xfft_2048_ip in scaled
    mode + Pipelined Streaming + 1 channel + no XK_INDEX/OVFLO doesn't expose
    those ports. xelab errored "cannot find port" on all four. Removed.
    run_xfft_xsim.sh missed -i "$PROJ_ROOT" so xvlog couldn't resolve
    `include "radar_params.vh"` from inside tb/. Fixed.
2026-05-02 test(fpga): PR-Q.2 — align cosim T_PRI_MEDIUM 175->161 us + regen goldens
    Mirror the PR-Q.1 PRI stagger (MEDIUM 175 us -> 161 us) into the cosim
    scenario generator and regenerate all 12 affected golden hex/csv files.
    Without this, the Doppler co-sim TBs would diverge from the RTL on every
    MEDIUM sub-frame bin.
    - tb/cosim/radar_scene.py: T_PRI_MEDIUM = 161e-6
    - tb/cosim/gen_doppler_golden.py: comment update for MEDIUM bin map
2026-05-02 fix(gui): P-4 — dashboard NUM_RANGE_BINS 64 → 512 (import from radar_protocol)
    dashboard.py:77 had a stale `NUM_RANGE_BINS = 64` literal from pre-PR-F.
    Range-Doppler canvas was mis-sized: parser at radar_protocol.py:425
    already enforces 512, so production frames would never have rendered
    correctly even with P-2/P-3 in place.
    Fix: drop the local literals; re-export NUM_RANGE_BINS / NUM_DOPPLER_BINS
    through v7/hardware.py (which already re-exports the rest of
2026-05-02 fix(gui): P-6 / PR-Q.6 — workers route detections through CRT extractor (C-5)
    Both live and replay paths used the legacy single-PRI extractor with the
    LONG-PRI v_res placeholder, which yielded wrong velocities for the SHORT
    and MEDIUM sub-frames. PR-Q.5 already provided extract_targets_from_frame_crt
    (48-bin, 3-PRI Chinese-Remainder-Theorem unfolding) — this PR wires it in.
    Changes:
    - workers.py imports extract_targets_from_frame_crt at module scope.
2026-05-02 sim(antenna): tune aperture-coupled v2 to design point — R matched, X residual documented
    10-iteration analytic-tune sweep (no DE optimizer — that was a wrong
    direction for this topology) on the Stack_Hybrid 4-layer stackup. Key
    findings from the sweep are baked into the script defaults and header.
    Best design point @ 10.5 GHz (now the env-var defaults):
    patch W=9.55 mm L=7.77 mm
    slot L=3.00 mm W=0.50 mm (centered under patch)
2026-05-04 chore(mcu): C-14a — delete dead ADF4382A EZSync surface
    Production firmware never used SYNC_METHOD_EZSYNC — both callsites
    (main.cpp:938 recovery, main.cpp:1955 boot) pass SYNC_METHOD_TIMED.
    The original audit C-14 flagged TX/RX SPI skew in EZSync's trigger
    sequence, but the path was dead from production; only test_bug3
    referenced it for spy-harness regression coverage.
    Removed:
2026-05-04 chore(tests): retire v1 cross-layer iverilog cosim tier
    The v1-era tb_cross_layer_ft2232h.v cosim TB no longer matches
    production after the protocol-v2 / opcode dispatch rework (PR-G).
    Equivalent v2 coverage now lives in the FPGA regression's
    tb_usb_protocol_v2.v and tb_system_opcodes.v.
    Removed:
    - tb_cross_layer_ft2232h.v (716 lines)
2026-05-04 fix(mcu): F-4.5 + F-4.6 — AD9523 heap/lifecycle hygiene
    F-4.5: ad9523_setup() malloc's both an ad9523_dev and a no_os SPI
    descriptor (ad9523.c:430,435). Previously the dev pointer was local
    to configure_ad9523() and fell out of scope on return — every
    recovery cycle (ERROR_AD9523_CLOCK → re-run configure_ad9523) leaked
    one struct + one SPI desc. STM32F7 heap is bounded; sustained
    brown-out flapping would eventually exhaust it. Move dev to a file-
2026-05-05 test(v7): port live-vs-replay physical-units parity guard from develop
    Adapts Serhii's TestLiveReplayPhysicalUnitsParity (f895c02 on develop) to
    the post-PR-Q.6 worker structure on feat/dual-range-v2.
    The original f895c02 fix was for a bug where RadarDataWorker._run_host_dsp
    read self._settings.velocity_resolution (RadarSettings default 1.0 m/s/bin)
    while ReplayWorker used WaveformConfig (~5.343 m/s/bin) — live GUI under-
    reported velocity by ~5.34x vs replay. PR-Q.6 unified both paths through
2026-05-05 fix(mcu): PR-W F-6.3 — clear opposite REG_MISC_ENABLES bit in setADTR1107Mode
    Latent bit-mask hygiene gap. setADTR1107Mode(TX) was asserting BIAS_EN
    (bit 5) without first clearing LNA_BIAS_OUT_EN (bit 4); the RX branch
    mirrored the bug. On any TX→RX→TX (or symmetric) transition through
    this register both PA and LNA bias outputs would end up enabled
    simultaneously. Production today only ever calls one direction at boot
    and the opposite at shutdown — never both during normal operation —
2026-05-05 docs(fpga): PR-X.2 F-7.2 — refresh adc_clk_mmcm.xdc comments to SDR IFF
    Constraint values are unchanged — only the explanatory comments are
    refreshed to match the post-AUDIT-C4 (2026-05-01) RTL.
    - "IDDR outputs" → "IFF Q output"
    - "adc_data_{rise,fall}_bufg" → "adc_data_iff_bufg"
    - "the IDDR ~1.4ns before the clock" → "the IOB-packed IFF ~1.4ns
    before the clock"
2026-05-07 feat(fpga,gui): PR-AC.1 — M-5 status pkt 30→34 B for medium_chirp/medium_listen readback
    Closes the 161-µs MEDIUM PRI visibility gap from the 2026-05-02 e2e audit.
    PR-G ran out of reserved bits in status_words[3] to fit a second 16-bit
    pair, so this PR adds status_words[7] = {medium_chirp[15:0], medium_listen[15:0]}
    and bumps STATUS_PKT_LEN 30→34, STATUS_PACKET_SIZE 30→34.
    RTL (usb_data_interface_ft2232h.v):
    - Two new input ports `status_medium_chirp` / `status_medium_listen`.
2026-05-11 PR-AB.b expanded commit 6: subframe_pulse strip + stale MCU DIAG cleanup
    Final cleanup pass for the PR-AB.b expanded bundle.
    chirp_scheduler.v / radar_receiver_final.v: delete the unused subframe_pulse
    output + its sibling subframe_id port. Both were declared on the scheduler
    and bound at the radar_receiver_final.sched instance, but no downstream
    module read them -- doppler_processor counts sub-frame boundaries
    internally from new_chirp_frame + CHIRPS_PER_SUBFRAME=16. The stale
2026-05-20 patch antenna KiCad
